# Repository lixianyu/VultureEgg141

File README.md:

# VultureEgg141
Based on TI BLE-CC254x-1.4.1.43908 stack

http://www.geek-workshop.com/thread-10164-1-1.html

VultureEgg project based on 'SensorTag' project.

***
## Service UUID : FFF0

## Command UUID : F0C1

## Trans   UUID : FFF6

***

### Enable FFF6 notify.

### Write F0C1 following command

#### Protocol between phone and VultureEgg:

- AB0101 -- Start LM75A and measurement period is the default value 20s.

- AB01010A -- Start LM75A and measurement period is 10s

- AB0100 -- Stop LM75A

- AB0201 -- Start humidity(SHT21) and measurement period is the default value 70s.

- AB02010F -- Start humidity(SHT21) and measurement period is 15s

- AB0200 -- Stop humidity(SHT21)

- AB0301 -- Start MPU6050 and measurement period is the default value 2s.

---
#### For example
> AB03010001 -- Start MPU6050 and measurement period is 1ms

> AB03010002 -- Start MPU6050 and measurement period is 2ms

> AB0301012C -- Start MPU6050 and measurement period is 300ms

> AB0300 -- Stop MPU6050

---
When disconnected, all measurement will be stopped.
---

##### About soft IIC:
```
#define SDA_GPIO P0_4
#define SCL_GPIO P0_1
```

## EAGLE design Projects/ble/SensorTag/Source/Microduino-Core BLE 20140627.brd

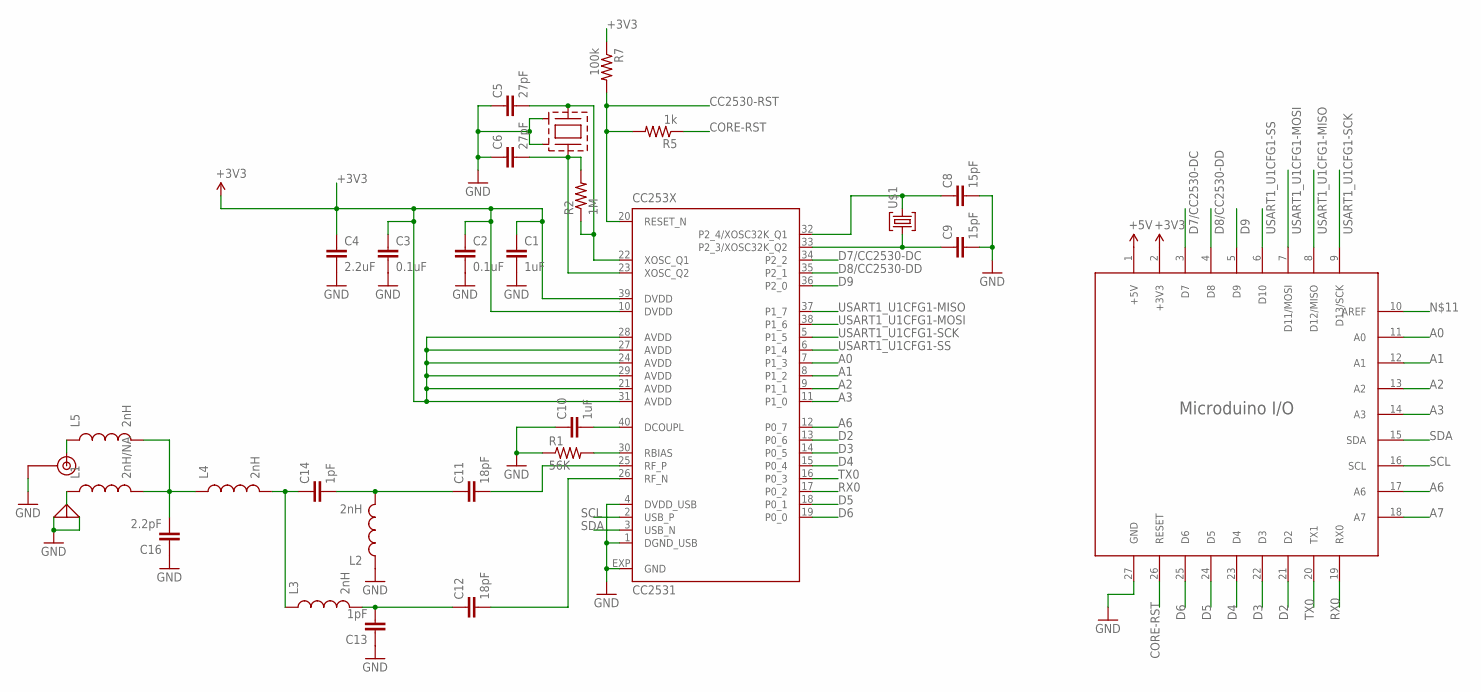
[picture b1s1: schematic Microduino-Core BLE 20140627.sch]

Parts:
C1, C10: 1uF; 0603-CAP
C2, C3: 0.1uF; 0402-CAP
C4: 2.2uF; 0402-CAP
C5, C6: 27pF; 0402-CAP
C8, C9: 15pF; 0402-CAP
C11, C12: 18pF; 0402-CAP
C13, C14: 1pF; 0402-CAP
C16: 2.2pF; 0402-CAP
CC253X: CC2531; RHA_S-PVQFN-N40
CRYS.1: CRYSTAL-SMD; CRYSTAL-SMD-3225
L1: 2nH/NA; C0402
L2, L3, L4, L5: 2nH; C0402
R1: 56K; 0402-RES
R2: 1M; 0402-RES
R5: 1k; 0402-RES
R7: 100k; 0402-RES
U$1: 32.768-3215; 3215-2PIN
U$2: ANT2.4G
U$3: ANT-IPEX; IPEX
U$7: MICRDUINO-PIN/NORMAL; 27UPIN-NORMAL

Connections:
+3V3: C1.1, C2.1, C3.1, C4.1, CC253X.10 (DVDD), CC253X.21 (AVDD), CC253X.24 (AVDD), CC253X.27 (AVDD), CC253X.28 (AVDD), CC253X.29 (AVDD), CC253X.31 (AVDD), CC253X.39 (DVDD), R7.1, U$7.2 (+3V3)
+5V: U$7.1 (+5V)
A0: CC253X.7 (P1_3), U$7.11 (A0)
A1: CC253X.8 (P1_2), U$7.12 (A1)
A2: CC253X.9 (P1_1), U$7.13 (A2)
A3: CC253X.11 (P1_0), U$7.14 (A3)
A6: CC253X.12 (P0_7), U$7.17 (A6)
A7: U$7.18 (A7)
CC2530-RST: CC253X.20 (RESET_N), R5.2, R7.2
CORE-RST: R5.1, U$7.26 (RESET)
D2: CC253X.13 (P0_6), U$7.21 (D2)
D3: CC253X.14 (P0_5), U$7.22 (D3)
D4: CC253X.15 (P0_4), U$7.23 (D4)
D5: CC253X.18 (P0_1), U$7.24 (D5)
D6: CC253X.19 (P0_0), U$7.25 (D6)
D7/CC2530-DC: CC253X.34 (P2_2), U$7.3 (D7)
D8/CC2530-DD: CC253X.35 (P2_1), U$7.4 (D8)
D9: CC253X.36 (P2_0), U$7.5 (D9)
GND: C1.2, C2.2, C3.2, C4.2, C5.1, C6.1, C8.2, C9.2, C10.1, C13.1, C16.1, CC253X.1 (DGND_USB), CC253X.4 (DVDD_USB), CC253X.EXP (GND), CRYS.1.2, CRYS.1.4, L2.1, R1.1, U$2.GND (GND2), U$3.1 (GND1), U$3.2 (GND2), U$7.27 (GND)
unnamed: C16.2, L1.2, L4.1, L5.2
unnamed: C10.2, CC253X.40 (DCOUPL)
unnamed: C5.2, CC253X.22 (XOSC_Q1), CRYS.1.1, R2.1
unnamed: C6.2, CC253X.23 (XOSC_Q2), CRYS.1.3, R2.2
unnamed: CC253X.30 (RBIAS), R1.2
unnamed: C11.2, CC253X.25 (RF_P)
unnamed: C12.2, CC253X.26 (RF_N)
unnamed: C11.1, C14.2, L2.2
unnamed: C12.1, C13.2, L3.2
unnamed: C14.1, L3.1, L4.2
unnamed: L1.1, U$3.3 (ANT)
unnamed: C8.1, CC253X.32 (P2_4/XOSC32K_Q1), U$1.P$2 (3)
unnamed: C9.1, CC253X.33 (P2_3/XOSC32K_Q2), U$1.P$1 (1)
unnamed: L5.1, U$2.ANT (IN)
RX0: CC253X.17 (P0_2), U$7.19 (RX0)
SCL: CC253X.2 (USB_P), U$7.16 (SCL)
SDA: CC253X.3 (USB_N), U$7.15 (SDA)
TX0: CC253X.16 (P0_3), U$7.20 (TX1)
USART1_U1CFG1-MISO: CC253X.37 (P1_7), U$7.8 (D12/MISO)
USART1_U1CFG1-MOSI: CC253X.38 (P1_6), U$7.7 (D11/MOSI)
USART1_U1CFG1-SCK: CC253X.5 (P1_5), U$7.9 (D13/SCK)
USART1_U1CFG1-SS: CC253X.6 (P1_4), U$7.6 (D10)

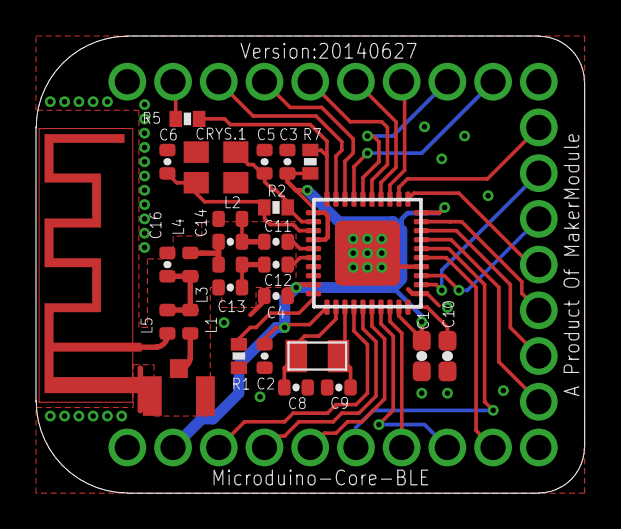
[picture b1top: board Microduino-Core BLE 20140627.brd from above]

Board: 2 copper layers, 30.5 x 25.4 mm, 29 parts (0 on the bottom side), 39 nets.

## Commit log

2016-02-26 * The base.
2016-02-26 * 湿度加完了，下一步加温度。
2016-02-26 * Add LM75A sensor.
2016-02-26 * Add MPU6050 code. Next step is to do test.
2016-02-26 * MDSerialAppSendNoti测试OK
2016-02-26 * delete Eagle
2016-02-27 * MPU6050工作了，先提交一下。
2016-02-27 * 测量SHT21时，不测量温度
2016-02-27 * 0.2.227 released.
2016-02-28 * 0.2.228 released. * Add documents.
2016-02-28 * Add protocol into README.md. * AB0101、AB0201、AB0301 can work, use the default measurement period.
2016-02-28 * VultureEgg_0.2.228.hex committed.
2016-02-28 * 默认period不对。
2016-02-29 * 去掉LED、KEY的编译开关 * 增加connection interval以降低蓝牙连接断开的几率。
2016-02-29 *Add some content in README.md.
2016-02-29 * 'VultureEgg_0.2.228_01.hex' --- this version work fine. Please use this version.
2016-10-01 * 为了适配蓝牙模块所做的更改，现在蓝牙模块可以连接“鸟蛋”了。而过去只能是手机连接鸟蛋。（蓝牙模块只去连接有FFF0 Service、FFF6特征值的从设备） * 因为蓝牙模块连接心跳间隔短，所以现在“鸟蛋”一旦启动之后即刻初始化MPU6050.否则在连接态初始化会导致断开连接。 * ABBB01 —— 可查看版本号； * ABBC01 —— 可查看MPU6050初始化时间； * ABBD01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
2016-10-19 对于Lysithea串口透传模块作为主设备时，它能够接受的从设备的连接参数最大为： DEFAULT_DESIRED_MIN_CONN_INTERVAL ： 80 DEFAULT_DESIRED_MAX_CONN_INTERVAL ： 96 DEFAULT_DESIRED_SLAVE_LATENCY ： 4
    否则，Lysithea这个主设备不会更新连接参数。不知为何。iPhone手机没有这个问题。
2016-10-19 0.2.A.18.11 released.
2016-12-14 AB03010001 -- start MPU6050, interval is 1ms;(0x0001) AB0401012C -- start MPU6050, interval is 300ms;(0x012C)
2016-12-14 Change Starting MPU6050 protocol
2018-01-23 Update README.md
    commit
2018-03-09 Create LICENSE
